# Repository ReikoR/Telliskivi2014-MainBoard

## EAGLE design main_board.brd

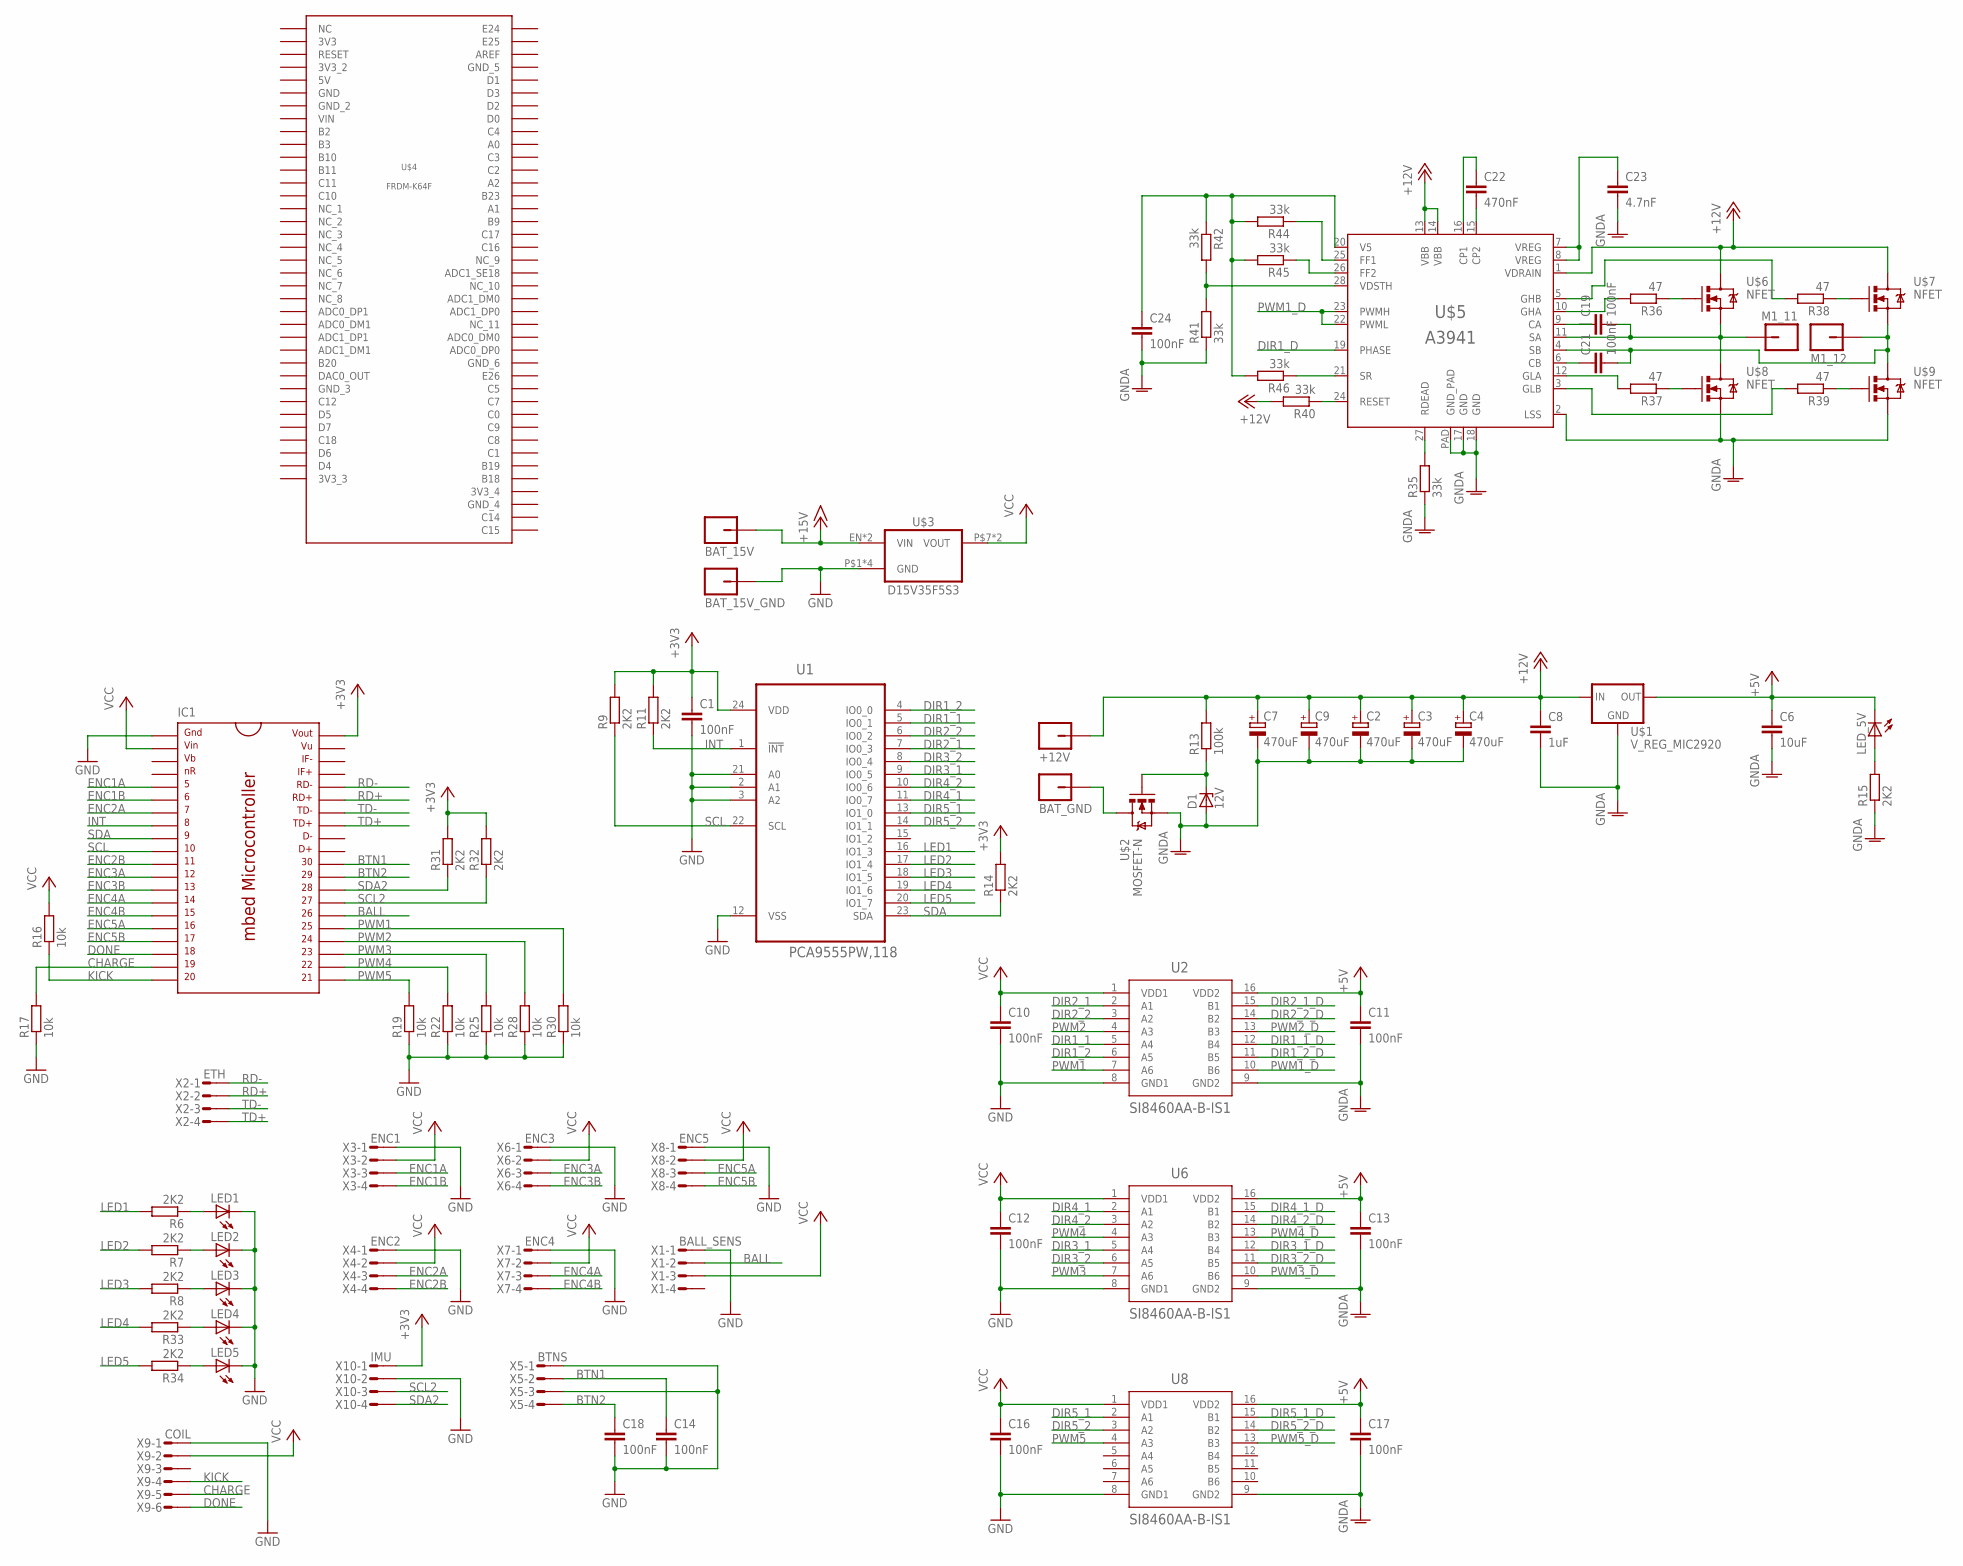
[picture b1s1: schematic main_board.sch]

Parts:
+12V: M01_PWR; PWR_HOLE
BAT_15V, BAT_15V_GND: M01_WIRE; WIRE_HOLE
BAT_GND: M01_PWR; PWR_HOLE
C1, C10, C11, C12, C13, C14, C16, C17, C18, C19, C21, C24: 100nF; C0603K
C2, C3, C4, C7, C9: 470uF; E3,5-8
C6: 10uF; C1206K
C8: 1uF; C0603K
C22: 470nF; C1206K
C23: 4.7nF; C1206K
D1: 12V; SOD123
IC1: MBED_MICROCONTROLLER; DIL40_0.9
LED1, LED2, LED3, LED4, LED5: LEDCHIP-LED0603; CHIP-LED0603
LED_5V: LEDCHIP-LED0603; CHIP-LED0603
M1_11, M1_12: M01_WIRE; WIRE_HOLE
R6, R7, R8, R9, R11, R14, R15, R31, R32, R33, R34: 2K2; R0603
R13: 100k; R0603
R16, R17, R19, R22, R25, R28, R30: 10k; R0603
R35, R40, R41, R42, R44, R45, R46: 33k; R0603
R36, R37, R38, R39: 47; R0603
U1: PCA9555PW,118; SOP65P640X110-24N
U2, U6, U8: SI8460AA-B-IS1; SOIC-16
U$1: V_REG_MIC2920; SOT223
U$2: MOSFET-N; TO127P600X120-5N
U$3: D15V35F5S3
U$4: FRDM-K64F
U$5: A3941
U$6, U$7, U$8, U$9: NFET; TO127P600X120-5N
X1: BALL_SENS; MICROMATCH-4
X2: ETH; MICROMATCH-4
X3: ENC1; MICROMATCH-4
X4: ENC2; MICROMATCH-4
X5: BTNS; MICROMATCH-4
X6: ENC3; MICROMATCH-4
X7: ENC4; MICROMATCH-4
X8: ENC5; MICROMATCH-4
X9: COIL; MICROMATCH-6
X10: IMU; MICROMATCH-4

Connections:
3V3: U$4.3V3
3V3_2: U$4.3V3_2
3V3_3: U$4.3V3_3
3V3_4: U$4.3V3_4
5V: U$4.5V
+3V3: C1.1, IC1.40, R9.2, R11.2, R14.2, R31.2, R32.2, U1.24 (VDD), X10.1
+5V: C6.1, C11.1, C13.1, C17.1, LED_5V.C, U2.16 (VDD2), U6.16 (VDD2), U8.16 (VDD2), U$1.3 (OUT)
+12V: +12V.P$1, C2.+, C3.+, C4.+, C7.+, C8.1, C9.+, R13.2, R40.2, U$1.1 (IN), U$5.1 (VDRAIN), U$5.13 (VBB), U$5.14 (VBB), U$6.5 (D), U$7.5 (D)
+15V: BAT_15V.P$1, U$3.EN (VIN), U$3.P$5 (VIN)
BALL: IC1.26, X1.2
BTN1: C14.1, IC1.30, X5.2
BTN2: C18.1, IC1.29, X5.4
CHARGE: IC1.19, R17.2, X9.5
DIR1_1: U1.5 (IO0_1), U2.5 (A4)
DIR1_1_D: U2.12 (B4)
DIR1_2: U1.4 (IO0_0), U2.6 (A5)
DIR1_2_D: U2.11 (B5)
DIR1_D: U$5.19 (PHASE)
DIR2_1: U1.7 (IO0_3), U2.2 (A1)
DIR2_1_D: U2.15 (B1)
DIR2_2: U1.6 (IO0_2), U2.3 (A2)
DIR2_2_D: U2.14 (B2)
DIR3_1: U1.9 (IO0_5), U6.5 (A4)
DIR3_1_D: U6.12 (B4)
DIR3_2: U1.8 (IO0_4), U6.6 (A5)
DIR3_2_D: U6.11 (B5)
DIR4_1: U1.11 (IO0_7), U6.2 (A1)
DIR4_1_D: U6.15 (B1)
DIR4_2: U1.10 (IO0_6), U6.3 (A2)
DIR4_2_D: U6.14 (B2)
DIR5_1: U1.13 (IO1_0), U8.2 (A1)
DIR5_1_D: U8.15 (B1)
DIR5_2: U1.14 (IO1_1), U8.3 (A2)
DIR5_2_D: U8.14 (B2)
DONE: IC1.18, X9.6
ENC1A: IC1.5, X3.3
ENC1B: IC1.6, X3.4
ENC2A: IC1.7, X4.3
ENC2B: IC1.11, X4.4
ENC3A: IC1.12, X6.3
ENC3B: IC1.13, X6.4
ENC4A: IC1.14, X7.3
ENC4B: IC1.15, X7.4
ENC5A: IC1.16, X8.3
ENC5B: IC1.17, X8.4
GND: BAT_15V_GND.P$1, C1.2, C10.2, C12.2, C14.2, C16.2, C18.2, IC1.1, LED1.C, LED2.C, LED3.C, LED4.C, LED5.C, R17.1, R19.1, R22.1, R25.1, R28.1, R30.1, U1.2 (A1), U1.3 (A2), U1.12 (VSS), U1.21 (A0), U2.8 (GND1), U6.8 (GND1), U8.8 (GND1), U$3.P$1 (GND), U$3.P$2 (GND), U$3.P$3 (GND), U$3.P$4 (GND), U$4.GND, X1.1, X3.1, X4.1, X5.1, X5.3, X6.1, X7.1, X8.1, X9.1, X10.2
GNDA: C2.-, C3.-, C4.-, C6.2, C7.-, C8.2, C9.-, C11.2, C13.2, C17.2, C23.2, C24.2, D1.A, R15.1, R35.1, R41.1, U2.9 (GND2), U6.9 (GND2), U8.9 (GND2), U$1.2 (GND), U$1.4 (GND), U$2.1 (S), U$2.2 (S), U$2.3 (S), U$5.2 (LSS), U$5.17 (GND), U$5.18 (GND), U$5.PAD (GND_PAD), U$8.1 (S), U$8.2 (S), U$8.3 (S), U$9.1 (S), U$9.2 (S), U$9.3 (S)
GND_2: U$4.GND_2
GND_3: U$4.GND_3
GND_4: U$4.GND_4
GND_5: U$4.GND_5
GND_6: U$4.GND_6
INT: IC1.8, R11.1, U1.1 (!INT)
KICK: IC1.20, R16.1, X9.4
LED1: R6.2, U1.16 (IO1_3)
LED2: R7.2, U1.17 (IO1_4)
LED3: R8.2, U1.18 (IO1_5)
LED4: R33.2, U1.19 (IO1_6)
LED5: R34.2, U1.20 (IO1_7)
unnamed: LED1.A, R6.1
unnamed: LED2.A, R7.1
unnamed: LED3.A, R8.1
unnamed: LED_5V.A, R15.2
unnamed: LED4.A, R33.1
unnamed: LED5.A, R34.1
unnamed: R37.1, U$8.4 (G)
unnamed: R38.1, U$7.4 (G)
unnamed: R39.1, U$9.4 (G)
unnamed: R36.1, U$6.4 (G)
unnamed: C21.1, U$5.6 (CB)
unnamed: D1.C, R13.1, U$2.4 (G)
unnamed: BAT_GND.P$1, U$2.5 (D)
unnamed: C19.2, M1_11.P$1, U$5.11 (SA), U$6.1 (S), U$6.2 (S), U$6.3 (S), U$8.5 (D)
unnamed: C21.2, M1_12.P$1, U$5.4 (SB), U$7.1 (S), U$7.2 (S), U$7.3 (S), U$9.5 (D)
unnamed: C19.1, U$5.9 (CA)
unnamed: R35.2, U$5.27 (RDEAD)
unnamed: R36.2, U$5.10 (GHA)
unnamed: R38.2, U$5.5 (GHB)
unnamed: R37.2, U$5.12 (GLA)
unnamed: R39.2, U$5.3 (GLB)
unnamed: C22.1, U$5.16 (CP1)
unnamed: C22.2, U$5.15 (CP2)
unnamed: C23.1, U$5.7 (VREG), U$5.8 (VREG)
unnamed: R41.2, R42.2, U$5.28 (VDSTH)
unnamed: C24.1, R42.1, R44.2, R45.2, R46.2, U$5.20 (V5)
unnamed: R45.1, U$5.26 (FF2)
unnamed: R40.1, U$5.24 (RESET)
unnamed: R44.1, U$5.25 (FF1)
unnamed: R46.1, U$5.21 (SR)
PWM1: IC1.25, R30.2, U2.7 (A6)
PWM1_D: U2.10 (B6), U$5.22 (PWML), U$5.23 (PWMH)
PWM2: IC1.24, R28.2, U2.4 (A3)
PWM2_D: U2.13 (B3)
PWM3: IC1.23, R25.2, U6.7 (A6)
PWM3_D: U6.10 (B6)
PWM4: IC1.22, R22.2, U6.4 (A3)
PWM4_D: U6.13 (B3)
PWM5: IC1.21, R19.2, U8.4 (A3)
PWM5_D: U8.13 (B3)
RD+: IC1.35, X2.2
RD-: IC1.36, X2.1
SCL: IC1.10, R9.1, U1.22 (SCL)
SCL2: IC1.27, R32.1, X10.3
SDA: IC1.9, R14.1, U1.23 (SDA)
SDA2: IC1.28, R31.1, X10.4
TD+: IC1.33, X2.4
TD-: IC1.34, X2.3
VCC: C10.1, C12.1, C16.1, IC1.2, R16.2, U2.1 (VDD1), U6.1 (VDD1), U8.1 (VDD1), U$3.P$7 (VOUT), U$3.P$8 (VOUT), X1.3, X3.2, X4.2, X6.2, X7.2, X8.2, X9.2
VIN: U$4.VIN

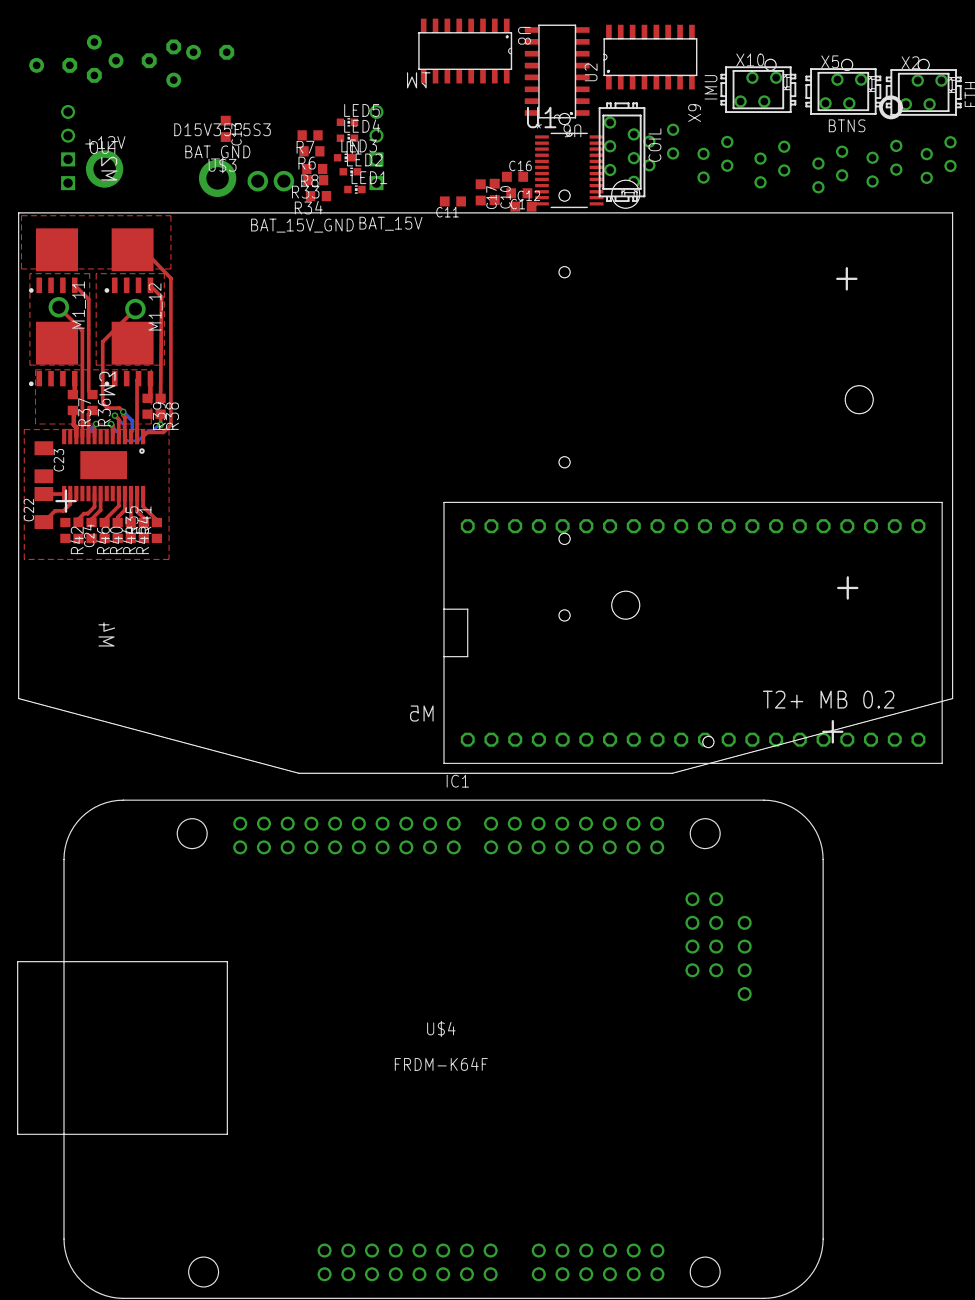
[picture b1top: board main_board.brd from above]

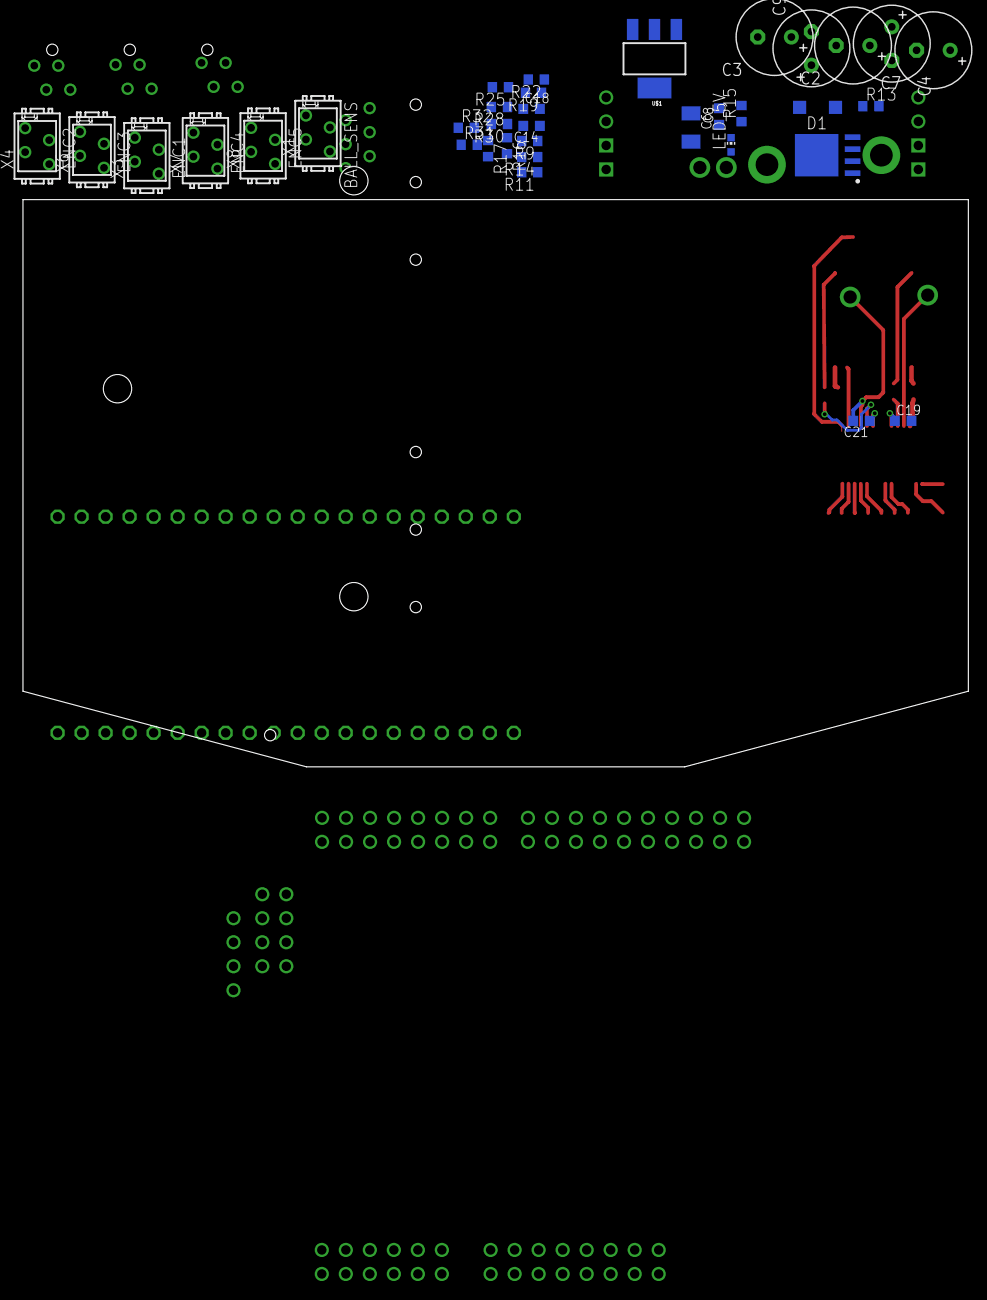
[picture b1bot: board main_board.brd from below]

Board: 2 copper layers, 100.0 x 60.0 mm, 88 parts (35 on the bottom side), 83 nets.

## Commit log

2014-08-16 Started planning
2014-08-17 Added one driver module

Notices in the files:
parts and their libraries:
SparkFun-PowerIC: Licensing: CC v3.0 Share-Alike You are welcome to use this library for commercial purposes.
